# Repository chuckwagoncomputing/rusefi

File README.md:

<div align="center">

<b>foo GPL open-source ECU</b>

</div>

# rusEFI

See [check.c](https://github.com/rusefi/rusefi/blob/master/firmware/check.c) for recommended version of GCC.

Current binaries are always available on our [build server](http://rusefi.com/build_server/)

[shop.rusEFI.com](https://www.shop.rusefi.com/)

# Cloning the repository
`git clone https://github.com/rusefi/rusefi.git`
Important note - we now use submodules:

`git submodule update --init`

# What do we have here?
 * [Firmware](/firmware) Source code for open source engine control unit for stm32 chips incuding [implementation overview](https://github.com/rusefi/rusefi/blob/master/firmware/readme.md)
 * [Hardware](/hardware) KiCAD files for our older PCBs
 * [rusEFI console](/java_console) rusEFI own naive tuning software
 * [Simulator](/simulator) win32 or posix version of firmware allows to explore without any hardware 
 * [Unit Tests](/unit_tests) Unit tests of firmware pieces
 * [Misc tools](/java_tools) Misc development utilities
 * [Software Development process](misc/SoftwareDevelopmentProcess.md)

# External Links

 * [Forum](http://rusefi.com/forum)
 * [Documentation](https://github.com/rusefi/rusefi/wiki)
 * [Doxygen documentation](http://rusefi.com/docs/html)
 * [General source code Q&A](http://rusefi.com/forum/viewtopic.php?f=5&t=10)
 * [Facebook](https://www.facebook.com/rusEfiECU)
 * [YouTube](https://www.youtube.com/user/rusefi)
 * [Patreon](https://www.patreon.com/rusefi)

# Building the Code
Check out https://rusefi.com/forum/viewtopic.php?f=5&t=9

# Release Notes

See [the changelog](firmware/CHANGELOG.md)

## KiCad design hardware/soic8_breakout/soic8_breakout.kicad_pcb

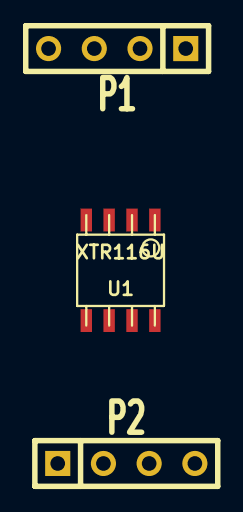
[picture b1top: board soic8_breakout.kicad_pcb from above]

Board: 2 copper layers, 3 parts (0 on the bottom side), 4 nets, no tracks yet.

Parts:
P1, P2: CONN_4; SIL-4
U1: XTR116U; so-8

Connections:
unnamed: P2.2, U1.6
unnamed: P1.3, U1.3
unnamed: P1.2, U1.2
unnamed: P1.1, U1.1

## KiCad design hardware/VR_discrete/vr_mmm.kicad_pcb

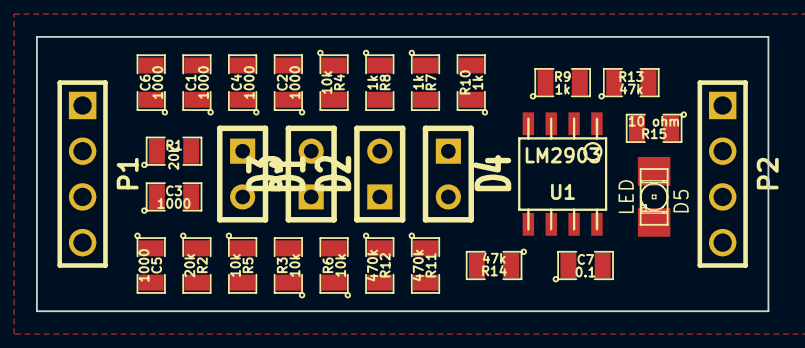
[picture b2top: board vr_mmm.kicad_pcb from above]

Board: 2 copper layers, 40.6 x 15.2 mm, 30 parts (0 on the bottom side), 13 nets, no tracks yet.

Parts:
C1, C2, C3, C4, C5, C6: 1000; SM0805
C7: 0.1; SM0805
D1, D2, D3, D4: SIL-2
D5: LED; LED-1206
P1, P2: CONN_4; PIN_ARRAY_4x1
R1, R2: 20k; SM0805
R3, R4, R5, R6: 10k; SM0805
R7, R8, R9, R10: 1k; SM0805
R11, R12: 470k; SM0805
R13, R14: 47k; SM0805
R15: 10 ohm; SM0805
U1: LM2903; so-8

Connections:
+5V: C7.1, P2.4, R9.2, R10.2, R13.1, R14.1, R15.2, U1.8
GND: C1.2, C2.2, C4.2, C6.2, C7.2, D5.2, P2.3, R7.1, R8.1, U1.4
unnamed: P2.2, R12.2, R14.2, U1.7
unnamed: D2.2, D4.1, R5.2, R12.1, U1.5
unnamed: D5.1, R15.1
unnamed: D2.1, D4.2, R6.2, R8.2, R10.1, U1.6
unnamed: C5.2, C6.1, P1.4, R2.2, R6.1
unnamed: C2.1, C5.1, P1.3, R2.1, R5.1
unnamed: D1.2, D3.1, R3.2, R11.1, U1.3
unnamed: D1.1, D3.2, R4.2, R7.2, R9.1, U1.2
unnamed: P2.1, R11.2, R13.2, U1.1
unnamed: C1.1, C3.1, P1.1, R1.1, R3.1
unnamed: C3.2, C4.1, P1.2, R1.2, R4.1

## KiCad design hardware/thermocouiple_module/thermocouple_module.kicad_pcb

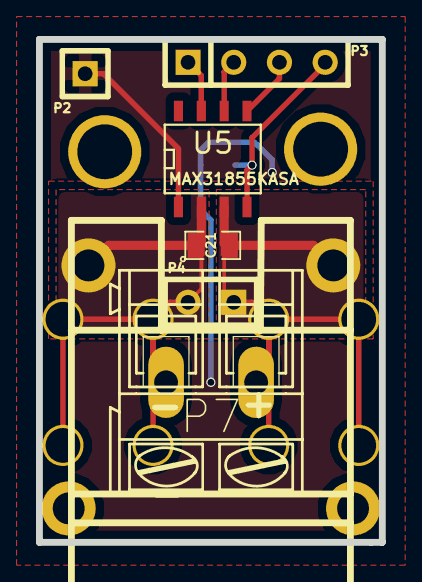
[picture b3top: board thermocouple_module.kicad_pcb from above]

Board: 2 copper layers, 19.0 x 27.9 mm, 12 parts (1 on the bottom side), 7 nets.

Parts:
C8: 100nF; SM0805-SM0603
C21: 10nF; SM0805-SM0603
P1: CONN_2; tcpl_PCC-SMP
P2: CONN_1; SIL-1
P3: CONN_4; SIL-4
P4: CONN_2; SIL-2
P5, P6: CONN_1; SCREW_TERM_534-7693
P7: CONN_2; AK300-2
U5: MAX31855KASA; SO8E
V801, V802: VIA; 1pin

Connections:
3.3v: C8.1, P3.4, U5.4
//CS: P3.2, U5.6
/MISO: P3.1, U5.7
/SCK: P3.3, U5.5
/TCPL+: C21.2, P1.2, P4.1, P6.1, P7.1, U5.3
/TCPL-: C21.1, P1.1, P4.2, P5.1, P7.2, U5.2
GND: C8.2, P2.1, U5.1

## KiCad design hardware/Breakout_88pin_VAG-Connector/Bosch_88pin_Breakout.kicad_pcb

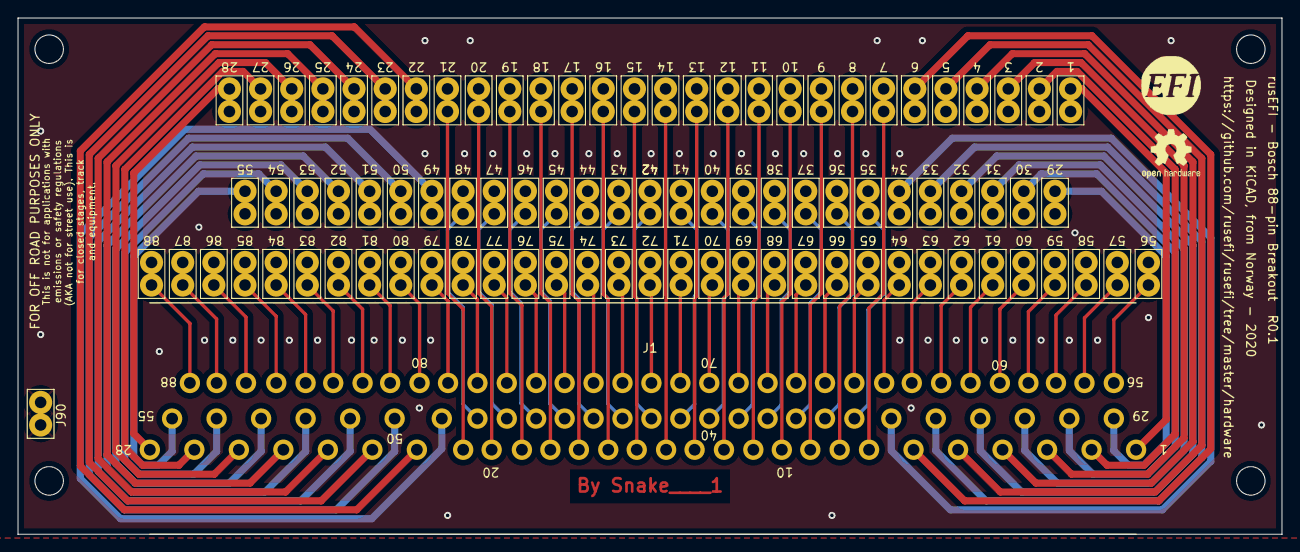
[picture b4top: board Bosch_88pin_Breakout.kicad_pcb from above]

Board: 2 copper layers, 142.0 x 58.0 mm, 97 parts (0 on the bottom side), 88 nets.

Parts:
G1: LOGO
G2: Disclaimer; Off_Road_Disclaimer
H1, H2, H3, H4: M3; MountingHole_3.2mm_M3_DIN965
J1: BOSCH_88PIN_02X44; BOSCH-88pin
J2: Pin1; TestPoint_Bridge_Pitch2.54mm_Drill1.3mm
J3: Pin3; TestPoint_Bridge_Pitch2.54mm_Drill1.3mm
J4: Pin5; TestPoint_Bridge_Pitch2.54mm_Drill1.3mm
J5: Pin7; TestPoint_Bridge_Pitch2.54mm_Drill1.3mm
J6: Pin9; TestPoint_Bridge_Pitch2.54mm_Drill1.3mm
J7: Pin11; TestPoint_Bridge_Pitch2.54mm_Drill1.3mm
J8: Pin13; TestPoint_Bridge_Pitch2.54mm_Drill1.3mm
J9: Pin15; TestPoint_Bridge_Pitch2.54mm_Drill1.3mm
J10: Pin17; TestPoint_Bridge_Pitch2.54mm_Drill1.3mm
J11: Pin19; TestPoint_Bridge_Pitch2.54mm_Drill1.3mm
J12: Pin21; TestPoint_Bridge_Pitch2.54mm_Drill1.3mm
J13: Pin23; TestPoint_Bridge_Pitch2.54mm_Drill1.3mm
J14: Pin25; TestPoint_Bridge_Pitch2.54mm_Drill1.3mm
J15: Pin27; TestPoint_Bridge_Pitch2.54mm_Drill1.3mm
J16: Pin29; TestPoint_Bridge_Pitch2.54mm_Drill1.3mm
J17: Pin31; TestPoint_Bridge_Pitch2.54mm_Drill1.3mm
J18: Pin33; TestPoint_Bridge_Pitch2.54mm_Drill1.3mm
J19: Pin35; TestPoint_Bridge_Pitch2.54mm_Drill1.3mm
J20: Pin37; TestPoint_Bridge_Pitch2.54mm_Drill1.3mm
J21: Pin39; TestPoint_Bridge_Pitch2.54mm_Drill1.3mm
J22: Pin41; TestPoint_Bridge_Pitch2.54mm_Drill1.3mm
J23: Pin43; TestPoint_Bridge_Pitch2.54mm_Drill1.3mm
J24: Pin45; TestPoint_Bridge_Pitch2.54mm_Drill1.3mm
J25: Pin47; TestPoint_Bridge_Pitch2.54mm_Drill1.3mm
J26: Pin49; TestPoint_Bridge_Pitch2.54mm_Drill1.3mm
J27: Pin51; TestPoint_Bridge_Pitch2.54mm_Drill1.3mm
J28: Pin53; TestPoint_Bridge_Pitch2.54mm_Drill1.3mm
J29: Pin55; TestPoint_Bridge_Pitch2.54mm_Drill1.3mm
J30: Pin57; TestPoint_Bridge_Pitch2.54mm_Drill1.3mm
J31: Pin59; TestPoint_Bridge_Pitch2.54mm_Drill1.3mm
J32: Pin61; TestPoint_Bridge_Pitch2.54mm_Drill1.3mm
J33: Pin63; TestPoint_Bridge_Pitch2.54mm_Drill1.3mm
J34: Pin65; TestPoint_Bridge_Pitch2.54mm_Drill1.3mm
J35: Pin67; TestPoint_Bridge_Pitch2.54mm_Drill1.3mm
J36: Pin69; TestPoint_Bridge_Pitch2.54mm_Drill1.3mm
J37: Pin71; TestPoint_Bridge_Pitch2.54mm_Drill1.3mm
J38: Pin73; TestPoint_Bridge_Pitch2.54mm_Drill1.3mm
J39: Pin75; TestPoint_Bridge_Pitch2.54mm_Drill1.3mm
J40: Pin77; TestPoint_Bridge_Pitch2.54mm_Drill1.3mm
J41: Pin79; TestPoint_Bridge_Pitch2.54mm_Drill1.3mm
J42: Pin81; TestPoint_Bridge_Pitch2.54mm_Drill1.3mm
J43: Pin83; TestPoint_Bridge_Pitch2.54mm_Drill1.3mm
J44: Pin85; TestPoint_Bridge_Pitch2.54mm_Drill1.3mm
J45: Pin87; TestPoint_Bridge_Pitch2.54mm_Drill1.3mm
J46: Pin2; TestPoint_Bridge_Pitch2.54mm_Drill1.3mm
J47: Pin4; TestPoint_Bridge_Pitch2.54mm_Drill1.3mm
J48: Pin6; TestPoint_Bridge_Pitch2.54mm_Drill1.3mm
J49: Pin8; TestPoint_Bridge_Pitch2.54mm_Drill1.3mm
J50: Pin10; TestPoint_Bridge_Pitch2.54mm_Drill1.3mm
J51: Pin12; TestPoint_Bridge_Pitch2.54mm_Drill1.3mm
J52: Pin14; TestPoint_Bridge_Pitch2.54mm_Drill1.3mm
J53: Pin16; TestPoint_Bridge_Pitch2.54mm_Drill1.3mm
J54: Pin18; TestPoint_Bridge_Pitch2.54mm_Drill1.3mm
J55: Pin20; TestPoint_Bridge_Pitch2.54mm_Drill1.3mm
J56: Pin22; TestPoint_Bridge_Pitch2.54mm_Drill1.3mm
J57: Pin24; TestPoint_Bridge_Pitch2.54mm_Drill1.3mm
J58: Pin26; TestPoint_Bridge_Pitch2.54mm_Drill1.3mm
J59: Pin28; TestPoint_Bridge_Pitch2.54mm_Drill1.3mm
J60: Pin30; TestPoint_Bridge_Pitch2.54mm_Drill1.3mm
J61: Pin32; TestPoint_Bridge_Pitch2.54mm_Drill1.3mm
J62: Pin34; TestPoint_Bridge_Pitch2.54mm_Drill1.3mm
J63: Pin36; TestPoint_Bridge_Pitch2.54mm_Drill1.3mm
J64: Pin38; TestPoint_Bridge_Pitch2.54mm_Drill1.3mm
J65: Pin40; TestPoint_Bridge_Pitch2.54mm_Drill1.3mm
J66: Pin42; TestPoint_Bridge_Pitch2.54mm_Drill1.3mm
J67: Pin44; TestPoint_Bridge_Pitch2.54mm_Drill1.3mm
J68: Pin46; TestPoint_Bridge_Pitch2.54mm_Drill1.3mm
J69: Pin48; TestPoint_Bridge_Pitch2.54mm_Drill1.3mm
J70: Pin50; TestPoint_Bridge_Pitch2.54mm_Drill1.3mm
J71: Pin52; TestPoint_Bridge_Pitch2.54mm_Drill1.3mm
J72: Pin54; TestPoint_Bridge_Pitch2.54mm_Drill1.3mm
J73: Pin56; TestPoint_Bridge_Pitch2.54mm_Drill1.3mm
J74: Pin58; TestPoint_Bridge_Pitch2.54mm_Drill1.3mm
J75: Pin60; TestPoint_Bridge_Pitch2.54mm_Drill1.3mm
J76: Pin62; TestPoint_Bridge_Pitch2.54mm_Drill1.3mm
J77: Pin64; TestPoint_Bridge_Pitch2.54mm_Drill1.3mm
J78: Pin66; TestPoint_Bridge_Pitch2.54mm_Drill1.3mm
J79: Pin68; TestPoint_Bridge_Pitch2.54mm_Drill1.3mm
J80: Pin70; TestPoint_Bridge_Pitch2.54mm_Drill1.3mm
J81: Pin72; TestPoint_Bridge_Pitch2.54mm_Drill1.3mm
J82: Pin74; TestPoint_Bridge_Pitch2.54mm_Drill1.3mm
J83: Pin76; TestPoint_Bridge_Pitch2.54mm_Drill1.3mm
J84: Pin78; TestPoint_Bridge_Pitch2.54mm_Drill1.3mm
J85: Pin80; TestPoint_Bridge_Pitch2.54mm_Drill1.3mm
J86: Pin82; TestPoint_Bridge_Pitch2.54mm_Drill1.3mm
J87: Pin84; TestPoint_Bridge_Pitch2.54mm_Drill1.3mm
J88: Pin86; TestPoint_Bridge_Pitch2.54mm_Drill1.3mm
J89: Pin88; TestPoint_Bridge_Pitch2.54mm_Drill1.3mm
J90: GND; TestPoint_Bridge_Pitch2.54mm_Drill1.3mm
LOGO1: Logo_Open_Hardware_Small; OSHW-Logo2_7.3x6mm_SilkScreen

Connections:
unnamed: J1.1, J2.1
unnamed: J1.2, J46.1
unnamed: J1.3, J3.1
unnamed: J1.4, J47.1
unnamed: J1.5, J4.1
unnamed: J1.6, J48.1
unnamed: J1.7, J5.1
unnamed: J1.8, J49.1
unnamed: J1.9, J6.1
unnamed: J1.10, J50.1
unnamed: J1.11, J7.1
unnamed: J1.12, J51.1
unnamed: J1.13, J8.1
unnamed: J1.14, J52.1
unnamed: J1.15, J9.1
unnamed: J1.16, J53.1
unnamed: J1.17, J10.1
unnamed: J1.18, J54.1
unnamed: J1.19, J11.1
unnamed: J1.20, J55.1
unnamed: J1.21, J12.1
unnamed: J1.22, J56.1
unnamed: J1.23, J13.1
unnamed: J1.24, J57.1
unnamed: J1.25, J14.1
unnamed: J1.26, J58.1
unnamed: J1.27, J15.1
unnamed: J1.28, J59.1
unnamed: J1.29, J16.1
unnamed: J1.30, J60.1
unnamed: J1.31, J17.1
unnamed: J1.32, J61.1
unnamed: J1.33, J18.1
unnamed: J1.34, J62.1
unnamed: J1.35, J19.1
unnamed: J1.36, J63.1
unnamed: J1.37, J20.1
unnamed: J1.38, J64.1
unnamed: J1.39, J21.1
unnamed: J1.40, J65.1
unnamed: J1.41, J22.1
unnamed: J1.42, J66.1
unnamed: J1.43, J23.1
unnamed: J1.44, J67.1
unnamed: J1.45, J24.1
unnamed: J1.46, J68.1
unnamed: J1.47, J25.1
unnamed: J1.48, J69.1
unnamed: J1.49, J26.1
unnamed: J1.50, J70.1
unnamed: J1.51, J27.1
unnamed: J1.52, J71.1
unnamed: J1.53, J28.1
unnamed: J1.54, J72.1
unnamed: J1.55, J29.1
unnamed: J1.56, J73.1
unnamed: J1.57, J30.1
unnamed: J1.58, J74.1
unnamed: J1.59, J31.1
unnamed: J1.60, J75.1
unnamed: J1.61, J32.1
unnamed: J1.62, J76.1
unnamed: J1.63, J33.1
unnamed: J1.64, J77.1
unnamed: J1.65, J34.1
unnamed: J1.66, J78.1
unnamed: J1.67, J35.1
unnamed: J1.68, J79.1
unnamed: J1.69, J36.1
unnamed: J1.70, J80.1
unnamed: J1.71, J37.1
unnamed: J1.72, J81.1
unnamed: J1.73, J38.1
unnamed: J1.74, J82.1
unnamed: J1.75, J39.1
unnamed: J1.76, J83.1
unnamed: J1.77, J40.1
unnamed: J1.78, J84.1
unnamed: J1.79, J41.1
unnamed: J1.80, J85.1
unnamed: J1.81, J42.1
unnamed: J1.82, J86.1
unnamed: J1.83, J43.1
unnamed: J1.84, J87.1
unnamed: J1.85, J44.1
unnamed: J1.86, J88.1
unnamed: J1.87, J45.1
unnamed: J1.88, J89.1

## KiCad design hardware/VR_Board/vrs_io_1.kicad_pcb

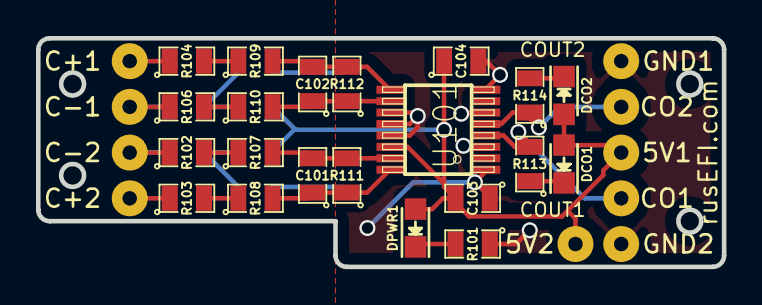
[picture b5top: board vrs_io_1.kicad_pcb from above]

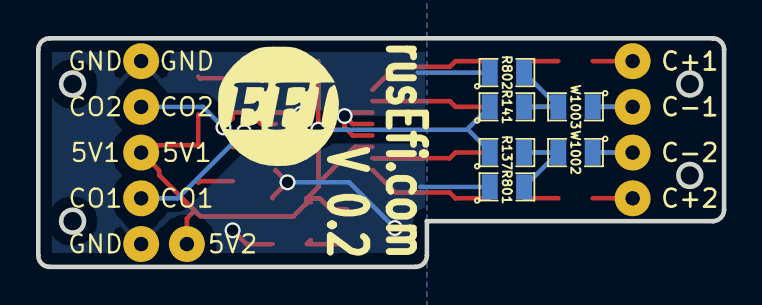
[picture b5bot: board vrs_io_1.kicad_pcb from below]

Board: 2 copper layers, 38.1 x 12.7 mm, 38 parts (11 on the bottom side), 21 nets.

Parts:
5V1, 5V2: CONN_01X01; SolderWirePad_single_0-8mmDrill
C101, C102: 1000pF; SM0805
C103: 10uF; SM0805
C104: 0.1uF; SM0805
C+1, C+2: CONN_01X01; SolderWirePad_single_0-8mmDrill
C-1, C-2: CONN_01X01; SolderWirePad_single_0-8mmDrill
CO1, CO2: CONN_01X01; SolderWirePad_single_0-8mmDrill
DCO1, DCO2: LED-red; LED_0805
DPWR1: LED-red; LED_0805
G?: LOGO; LOGO_F
GND1, GND2: CONN_01X01; SolderWirePad_single_0-8mmDrill
R101, R113, R114: 10k; SM0805
R102, R103, R104, R106, R107, R108, R109, R110, R111, R112: 5k; SM0805
R137, R141: 1K; SM0805
R801, R802: pdwn; SM0805
U101: MAX9926/9927; maxim-10-QSOP16
W1002, W1003: JMP; SM0805

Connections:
/5V: 5V1.1, 5V2.1, C103.2, C104.1, DCO1.2, DCO2.2, DPWR1.2, R137.1, R141.1, U101.14
/CAM+: C+1.1, R104.1
/CAM-: C-1.1, R106.1, W1003.1
/CRK2+: C+2.1, R103.1
/CRK2-: C-2.1, R102.1, W1002.1
/Cout1: CO1.1, R113.2, U101.4
/Cout2: CO2.1, R114.1, U101.5
GND: C103.1, C104.2, GND1.1, GND2.1, R101.1, R801.1, R802.1, U101.1, U101.3, U101.6, U101.8, U101.11, U101.12, U101.13
unnamed: C101.1, R108.2, R111.1, U101.16
unnamed: C101.2, R107.2, R111.2, U101.15
unnamed: C102.1, R110.2, R112.1, U101.10
unnamed: C102.2, R109.2, R112.2, U101.9
unnamed: DCO1.1, R113.1
unnamed: DCO2.1, R114.2
unnamed: DPWR1.1, R101.2
unnamed: R102.2, R107.1
unnamed: R103.2, R108.1
unnamed: R104.2, R109.1
unnamed: R106.2, R110.1
unnamed: R137.2, R801.2, W1002.2
unnamed: R141.2, R802.2, W1003.2

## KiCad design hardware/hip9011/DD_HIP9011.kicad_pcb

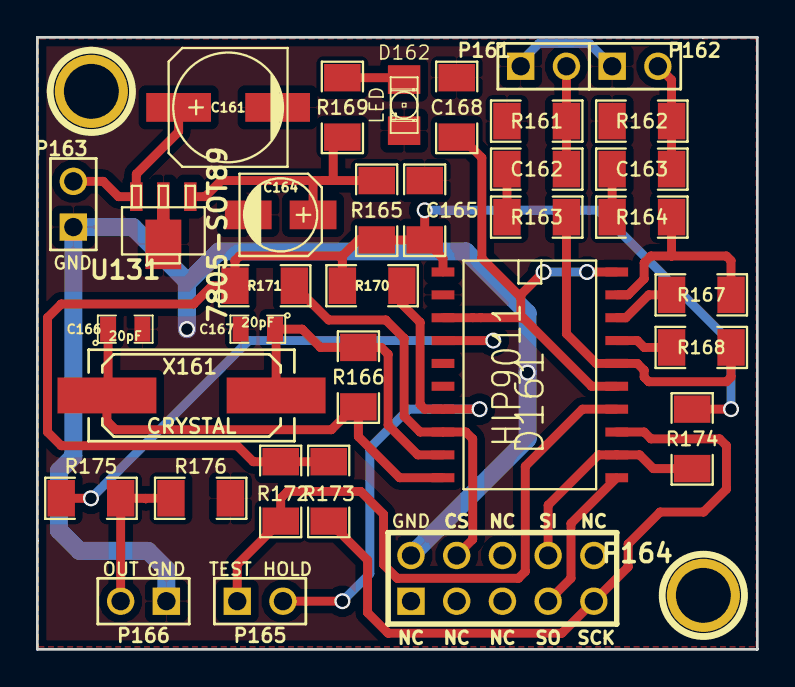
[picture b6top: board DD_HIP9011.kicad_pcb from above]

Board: 2 copper layers, 40.0 x 34.0 mm, 35 parts (1 on the bottom side), 24 nets.

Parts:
C161: 100u; c_elec_6.3x5.3
C162, C163: 47n; SM1206
C164: 10u; c_elec_4x5.3
C165: 100n; SM1206
C166, C167: 20pF; SM0805
C168: 22n; SM1206
D161: HIP9011; SO20L
D162: LED; LED-1206
G161: LOGO; LOGO_F
P161: KNOCK 1; PIN_ARRAY_2X1
P162: KNOCK 2; PIN_ARRAY_2X1
P163: 12V; PIN_ARRAY_2X1
P164: CONN_5X2; PIN_ARRAY_5x2
P165, P166: CONN_2; PIN_ARRAY_2X1
R161, R162, R166: 1M; SM1206
R163, R164, R175, R176: 10k; SM1206
R165: 10R; SM1206
R167, R168: 68k; SM1206
R169: 470R; SM1206
R170, R171, R172, R173, R174: 1K; SM1206
U131: 7805-SOT89; sot89
X161: CRYSTAL; Q_49U3HMS

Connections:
/5V: C165.1, D161.1, R165.2, R170.1, R171.1, R172.1, R173.1, R174.1
/+12V: C161.1, P163.2, U131.3
/CS: D161.8, P164.4, R171.2
/GND: C161.2, C164.2, C165.2, C166.2, C167.2, C168.2, D161.2, D162.2, P161.1, P162.1, P163.1, P164.2, P166.1, R161.2, R162.2, R176.2, U131.2
/INT/HLD: D161.7, P165.2, R170.2
/INTOUT: D161.4, R175.1
/KNOCK1: C162.1, P161.2, R161.1
/KNOCK2: C163.1, P162.2, R162.1
/OUT: P166.2, R175.2, R176.1
/SCK: D161.13, P164.9, R173.2
/SI: D161.12, P164.8, R174.2
/SO: D161.11, P164.7
/TEST: D161.14, P165.1, R172.2
unnamed: D162.1, R169.1
unnamed: C164.1, R165.1, R169.2, U131.1
unnamed: C167.1, D161.9, R166.2, X161.1
unnamed: C166.1, D161.10, R166.1, X161.2
unnamed: C163.2, R164.1
unnamed: C168.1, D161.3, D161.15, D161.20
unnamed: D161.16, R163.2, R168.2
unnamed: D161.17, R168.1
unnamed: D161.18, R167.1
unnamed: D161.19, R164.2, R167.2
unnamed: C162.2, R163.1

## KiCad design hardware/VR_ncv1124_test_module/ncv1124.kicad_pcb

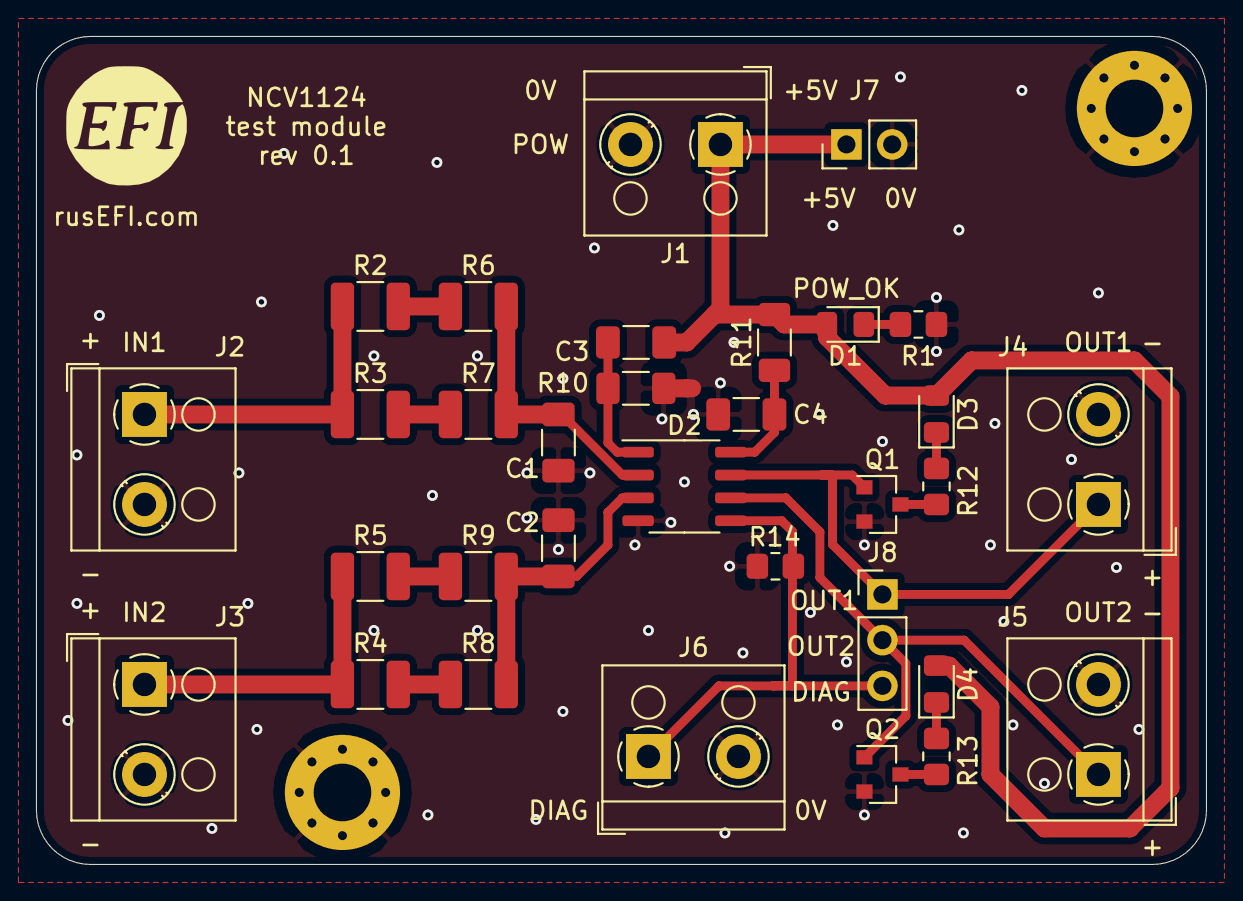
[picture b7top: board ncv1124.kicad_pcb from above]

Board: 2 copper layers, 65.0 x 46.0 mm, 35 parts (0 on the bottom side), 20 nets.

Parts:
C1, C2, C3: 0.022u; C_1206_3216Metric_Pad1.33x1.80mm_HandSolder
C4: 0.22u; C_1206_3216Metric_Pad1.33x1.80mm_HandSolder
D1, D3, D4: LED; LED_0805_2012Metric_Pad1.15x1.40mm_HandSolder
D2: NCV1124; SO-8_3.9x4.9mm_P1.27mm
G1: LOGO
H1, H2: MountingHole_Pad; MountingHole_3.2mm_M3_Pad_Via
J1, J2, J3, J4, J5, J6: Screw_Terminal_01x02; TerminalBlock_RND_205-00001_1x02_P5.00mm_Horizontal
J7: Conn_01x02_Male; PinHeader_1x02_P2.54mm_Vertical
J8: Conn_01x03_Male; PinHeader_1x03_P2.54mm_Vertical
Q1, Q2: 2N7002; SOT-23
R1, R12, R13, R14: 3K; R_0805_2012Metric_Pad1.20x1.40mm_HandSolder
R2, R3, R4, R5, R6, R7, R8, R9: 22k; R_1210_3225Metric_Pad1.30x2.65mm_HandSolder
R10: 24k; R_1206_3216Metric_Pad1.30x1.75mm_HandSolder
R11: 39; R_1206_3216Metric_Pad1.30x1.75mm_HandSolder

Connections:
+5V: C3.1, D1.2, D3.2, D4.2, J1.1, J7.1, R11.2
GND: C1.2, C2.2, C4.2, D2.4, H1.1, H2.1, J1.2, J2.2, J3.2, J4.2, J5.2, J6.2, J7.2, Q1.2, Q2.2, R1.1, R10.1, R14.1
unnamed: C1.1, D2.2, R6.2, R7.2
unnamed: C2.1, D2.3, R8.2, R9.2
unnamed: C3.2, D2.1, R10.2
unnamed: C4.1, D2.8, R11.1
unnamed: D1.1, R1.2
unnamed: D2.5, J6.1, J8.3, R14.2
unnamed: D2.6, J5.1, J8.2, Q2.1
unnamed: D2.7, J4.1, J8.1, Q1.1
unnamed: D3.1, R12.2
unnamed: D4.1, R13.2
unnamed: J2.1, R2.1, R3.1
unnamed: J3.1, R4.1, R5.1
unnamed: Q1.3, R12.1
unnamed: Q2.3, R13.1
unnamed: R2.2, R6.1
unnamed: R3.2, R7.1
unnamed: R4.2, R8.1
unnamed: R5.2, R9.1

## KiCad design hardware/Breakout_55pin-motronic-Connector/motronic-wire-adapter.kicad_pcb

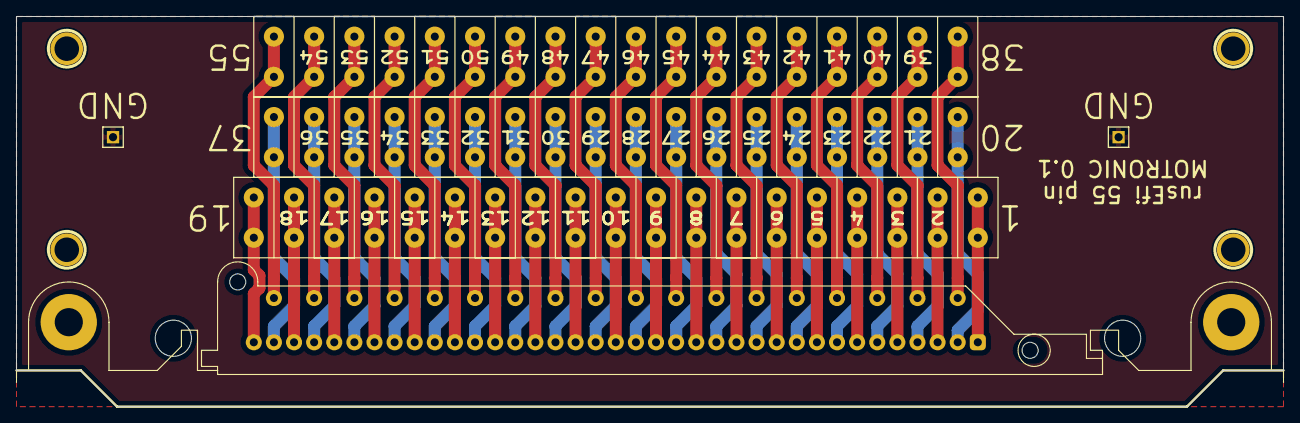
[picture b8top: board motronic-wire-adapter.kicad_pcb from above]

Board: 2 copper layers, 157.5 x 48.5 mm, 10 parts (0 on the bottom side), 56 nets.

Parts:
1PIN, 1PIN#2, 1PIN#3, 1PIN#4: P***; 1pin
P1: MOTRONIC; 55pin_china_bosch_motronic
P2: CONN_19; CON19X5
P3, P4: CONN_18; CON18X5
P5, P6: CONN_1; PIN_ARRAY_1

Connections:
GND: P5.1, P6.1
unnamed: P1.11, P2.11
unnamed: P1.1, P2.1
unnamed: P1.2, P2.2
unnamed: P1.3, P2.3
unnamed: P1.4, P2.4
unnamed: P1.5, P2.5
unnamed: P1.6, P2.6
unnamed: P1.7, P2.7
unnamed: P1.8, P2.8
unnamed: P1.9, P2.9
unnamed: P1.10, P2.10
unnamed: P1.55, P4.18
unnamed: P1.12, P2.12
unnamed: P1.13, P2.13
unnamed: P1.14, P2.14
unnamed: P1.15, P2.15
unnamed: P1.16, P2.16
unnamed: P1.17, P2.17
unnamed: P1.18, P2.18
unnamed: P1.19, P2.19
unnamed: P1.20, P3.1
unnamed: P1.21, P3.2
unnamed: P1.44, P4.7
unnamed: P1.34, P3.15
unnamed: P1.35, P3.16
unnamed: P1.36, P3.17
unnamed: P1.37, P3.18
unnamed: P1.38, P4.1
unnamed: P1.39, P4.2
unnamed: P1.40, P4.3
unnamed: P1.41, P4.4
unnamed: P1.42, P4.5
unnamed: P1.43, P4.6
unnamed: P1.22, P3.3
unnamed: P1.45, P4.8
unnamed: P1.46, P4.9
unnamed: P1.47, P4.10
unnamed: P1.48, P4.11
unnamed: P1.49, P4.12
unnamed: P1.50, P4.13
unnamed: P1.51, P4.14
unnamed: P1.52, P4.15
unnamed: P1.53, P4.16
unnamed: P1.54, P4.17
unnamed: P1.33, P3.14
unnamed: P1.23, P3.4
unnamed: P1.24, P3.5
unnamed: P1.25, P3.6
unnamed: P1.26, P3.7
unnamed: P1.27, P3.8
unnamed: P1.28, P3.9
unnamed: P1.29, P3.10
unnamed: P1.30, P3.11
unnamed: P1.31, P3.12
unnamed: P1.32, P3.13

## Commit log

2020-05-23 TLE migration
2020-05-23 Revert "hiding diag code which was messing with GP2/GP3 i.e. TLE8888_PIN_22 TLE8888_PIN_23"
    This reverts commit 75781f12
2020-06-18 removed duplicated workflow
2020-06-18 test
2021-01-25 set debug mode
2021-03-05 Auto-generated configs and docs
2021-06-12 tcu input config
2021-06-12 unused TS info
2021-06-12 am confuse
2021-06-12 add some logic
2021-06-12 change buttonshift to how I want it to work
2021-06-12 add arrays
2021-06-12 rebase
2021-06-12 add ROLE_ to avoid conflict
2021-06-12 config
2021-06-12 add parameters
2021-06-12 init logic
2021-06-12 why is this so hard
2021-06-12 me know c gud
2021-06-12 default returns
2021-06-12 why do I have to keep rebasing the same file
2021-06-12 does this work?
2021-06-12 help I'm stuck in a loop factory
2021-06-12 I have no idea
2021-06-12 find the current state
2021-06-12 I promise I can spell
2021-06-12 switch to CONFIG
2021-06-12 float is 32 i think
2021-06-12 try to add filler
2021-06-12 add tcuAnalogInputTolerance
2021-06-12 allow -1 value
2021-06-12 switch type
2021-06-12 try adding TS info
2021-06-12 update firmware
2021-06-12 undo accidental files
2021-06-12 ghost of christmas past
2021-06-12 oops how did that happen
2021-06-12 fix enum
2021-06-12 not understanding git frustrates me
2021-06-12 whyyyyyyy
2021-06-12 ok ok
2021-06-12 use arrays
2021-06-12 spaces?
2021-06-12 no whitespac..e
2022-07-01 calculate TC ratio
2022-07-01 add range selector matrix
2022-07-01 use for loop
2022-07-01 add generic gear controller class
2022-07-01 find range
2022-07-01 add manual plus/minus
2022-07-01 a few more range tweaks
2022-07-01 try to fix rusefi_config
2022-07-01 use isBrainPinValid
2022-07-01 move range array finding to function
2022-07-01 add a bit of manual gear handling logic
2022-07-01 a few range tweaks
2023-02-20 Bump chuckwagoncomputing/interactive-pinout from 2.0 to 2.1
    Bumps [chuckwagoncomputing/interactive-pinout](https://github.com/chuckwagoncomputing/interactive-pinout) from 2.0 to 2.1.
    - [Release notes](https://github.com/chuckwagoncomputing/interactive-pinout/releases)
    - [Commits](https://github.com/chuckwagoncomputing/interactive-pinout/compare/2.0...2.1)
    ---
    updated-dependencies:
    - dependency-name: chuckwagoncomputing/interactive-pinout
2023-02-21 Use read to store as var
2023-02-27 switch to kicad 7.0 ppa
2023-02-27 use 7 for iboms
2023-03-08 change check
2023-03-10 bump 7.0
2023-03-11 update ibom
2023-03-11 add workflow dispatch
2023-03-11 use single quotes
2023-03-11 use function
2023-03-11 correct var
2023-03-11 ignore prl
2023-03-11 convert to kicad 7
2023-03-11 test bump
2023-03-11 kicad libs branch
2023-03-12 test poke
2023-03-12 update pcb files
2023-03-12 poke
2023-07-18 bump
2023-07-18 try to make happy
2024-02-24 call gen_config_board with make
2024-02-26 add ts plugin launcher rules
2024-03-04 Generate docs and enums with make
2024-03-04 add make config command
2024-03-04 find build targets automatically
2024-03-04 get submodules the make way
2024-03-06 Explicitly generate .deps
2024-03-08 add encrypted bundle
2024-03-08 Use custom board build for main firmware workflow
2024-03-16 simulator has rules
2024-03-17 Update date
2024-03-17 only:simulator has BOARDS_DIR
2024-03-17 include board.mk
2024-03-17 only:pulling lines up
2024-03-17 check board-specific stuff in new makefile
2024-03-21 use META_OUTPUT_ROOT_FOLDER for ini upload
2024-03-21 Auto-generated default tune
2024-03-22 only: test
2024-03-22 only: test2
2024-03-22 only: test3
2024-03-25 this is
    a test
    of a
    multi line commit
    with a " for good measure
    and even a '
2024-03-27 make simulator depend on config files
2024-03-27 revamp pushing in workflows with pull --rebase
2024-04-20 test debian
2024-04-26 only: test4
2024-04-26 only: test5
2024-04-26 only: test6
2024-04-26 only: test7
2024-04-26 only: test8
2024-04-26 Revert "only: test8"
    This reverts commit ce13b6fa86eecd92ee35e284b3185711be140f22.
2024-04-26 only: test9
2024-06-21 Revert "custom boards build both linux and windows simulators always with full compilation #6585"
    This reverts commit d795855d8cba6cc68f984ecfcee8dfe9fc20f95b.
2024-06-21 only build exe first if requested
2024-11-04 use interpolate branch
2024-11-04 remove coords from proteus black23
2024-11-04 debug
2024-11-04 remove coords from alphax-8chan A-B
2025-10-09 Revert "only:gcc13 #6452"
    This reverts commit 9cb308b09d569e2bdf5bd1a26c8d0448fdfc7067.
2025-10-09 Don't enable LUA_LOOKUP for simulator if board has disabled it
2025-10-09 Give Proteus TCU its own prepend.txt to enable TS interface, enable LUA_LOOKUP
2026-02-10 Gen configs for console
2026-02-10 Remove all EFI_MAIN_RELAY_CONTROL definitions
    Always enable EFI_MAIN_RELAY_CONTROL behavior in MainRelayController
2026-02-10 Remove dead EFI_MAIN_RELAY_CONTROL code
2026-02-10 Shutdown engine when ignition voltage is lost
2026-02-18 Switch to msys2 for windows workflows
2026-03-16 Export remaining necessary info to triggers.txt
2026-03-16 Create script to convert triggers.txt to yaml [slop]
2026-03-16 Export angles with more digits
2026-03-16 Export isSynchronizationNeeded as boolean
2026-03-16 Triggers yaml
2026-03-16 Tweak tri-tach
2026-03-22 Read triggers.yaml
2026-03-22 Reset switchTimes and waveForm arrays
2026-03-23 Process triggers in MetaHelper
2026-03-23 Remove redundant knownOperationModes and operationModes
2026-03-23 Use initializeTriggerWaveform directly in tests
2026-03-24 Generate trigger decoder cpp
2026-03-24 Fix tests
2026-03-24 Adjust tests
2026-03-24 Add generated triggers to makefiles
2026-03-24 Build trigger_type_e_enum from triggers.yaml
2026-03-24 Get operation mode from trigger
2026-03-24 Copy names from TriggerImage.java to triggers.yaml
2026-03-24 Don't show TDC if shapeWithoutTdc
2026-03-24 Remove old trigger C
2026-03-24 Just get the name from triggerWheelInfo
2026-03-24 Hide disabled triggers
2026-03-24 Allow multiple input triggers files
2026-03-24 Fix validation errors
2026-03-24 Generate trigger_type_e enum from YAML [slop]
2026-03-24 Document triggers.yaml
2026-03-24 Validate triggers.yaml [slop]
2026-03-24 Remove and don't generate triggers.txt
2026-04-10 Generate configs first
    Generate config before building TS plugin
    Generate config before building rusEFI console
    reorder configs and docs-enums
    configs before docs
2026-04-10 Let make handle jar building in gen config workflow
2026-04-10 Let make handle jar and live doc building in console workflow
2026-04-10 Make perf trace enum generator separate gradle project
2026-04-10 remove tunerstudio and controllers generated
2026-04-10 Don't commit tunerstudio and controller generated
2026-04-10 Create java enum directory if it doesn't exist
2026-04-10 Remove generated java
2026-04-10 Remove generated lua value lookup
2026-04-10 Don't commit java
2026-04-10 Don't commit lua generated
2026-04-10 Remove console binary generated
2026-04-10 Don't commit console binary generated
2026-04-10 Remove generated board-specific code
2026-04-10 Remove commit step
2026-04-10 Don't commit generated board-specific code
2026-04-10 Set date at build time
2026-04-10 Remove auto_generated cpp and h
